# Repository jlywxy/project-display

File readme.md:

# Project Display

This is the repo sharing some of the mobile display information and their debugging method.<br>
The testing and debugging procedure are all from scratch, including PCB and firmware.<br>
See each dir for more info.<br>
*Note: <b>Display Module Specification or Display Interface Specification are NOT supplied.</b><br>

License: GPLv2<br>

Display Interface|Display Type|Brand|Bridge|Size|Part No.|Link
-|-|-|-|-|-|-
JEIDA LVDS|LCD|AUO|FPGA|7.0|G070VW01 V0|<a href='//github.com/jlywxy/project-display/lvds-lcd-auo-fpga'>lvds-lcd-auo-fpga</a>
MIPI DSI|LCD|Sharp|SSD2828|5.0|LS050T1SX01|<a href='//github.com/jlywxy/project-display/mipi-lcd-sharp-ssd2828'>mipi-lcd-sharp-ssd2828</a>
RGB UPS051|LCD|AUO|FPGA|3.0|A030DW01 / A030DW02|<a href='//github.com/jlywxy/project-display/parallel-lcd-auo-fpga'>parallel-lcd-auo-fpga</a>
RGB|LCD|LG Display|CPLD/FPGA|5.0|LD050WV1-SD01|<a href='//github.com/jlywxy/project-display/rgb-lcd-lg-cpld'>rgb-lcd-lg-cpld</a>
RGB|LCD|LG Display|STM32|5.0|LD050WV1-SD01|<a href='//github.com/jlywxy/project-display/rgb-lcd-lg-stm32'>rgb-lcd-lg-stm32</a>

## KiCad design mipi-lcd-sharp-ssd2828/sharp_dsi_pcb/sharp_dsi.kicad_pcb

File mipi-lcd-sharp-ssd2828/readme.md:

# Driving MIPI-DSI LCD(Sharp LS050T1SX01) using SSD2828

This project is testing the PCB layout of MIPI D-PHY high-speed differential and driving Sharp LS050T1SX01 using SSD2828 D-PHY and DSI bridge(Solomon Systech) and STM32F030F4 from scratch.

Author: jlywxy (jlywxy@outlook.com)<br>
Document Version: 1.4
- --
## Signal Wiring Brief
```
(any)  |  
       | < (parallel RGB)
       v
    SSD2828 ---------> Sharp LS050T1SX01
       ^       ^ (MIPI D-PHY & DSI)
       | < (SPI)
STM32  |  
```
- --
## Intention of the project
1. A PCB is made and tested, with MIPI D-PHY high-speed differential layouts and reverse voltage generator circuits.<br>
Checkout <a href="sharp_dsi_pcb">sharp_dsi_pcb</a> directory for PCB designed using KiCad.
2. Test method is using SSD2828 BIST mode and LCD bist mode (provided by LCD driver R63311) to display color at full screen and using the builtin test mode in the LCD. <br>
The testing signal frequency output from SSD2828 is now 992 MHz (0.99GHz), with ideal frame rate at 120 Hz.<br>

- --

## Circuit Schematic Suggestions

1. Use reverse voltage generator IC for LCD AVDD+/-.<br>
Currently using ICL7660 from Renesas.
2. Put KiCad PWR_FLAG at VBUS/GND at USB-C connector.
3. Use 3.3v LDO to VDDIO for LCD, SSD2828 and STM32.
- --

## High-Speed Signal Integrity for D-PHY

1. The board in this project is 2-layered, with the coplanar impedance control.<br>
2. Make sure D-PHY differential wiring has 100-Ohm differential impedance and 50-Ohm single end impedance. ()<br>
The width and space of the wiring should be calculated by the PCB impedance calculator or EDA-integrated tools. <br>
In this board, the Coplanar Differential Impedance is used. Since the restriction of 2-layer board, <b>the final impedance was controlled as 100-Ohm differential and 68-Ohm single-ended.</b><br>

* Note: for the difference of MIPI DSI and MIPI D-PHY, refer to `Misc->Knowledge Bases of Concepts` in this article.

## PCB Layout and Manufacturing Suggestions
1. For D-PHY Differential Layout
* Use a professional tool to design such a high-speed board, such as KiCad(using in this project)/Altium/Cadence.
* The D-PHY lines have to use vias going into the internal space of the connector.
```
------------------......
| | | | | | |
 ø ø ø ø ø ø ......
ø ø ø ø ø ø 
 | | | | | | | ......
------------------

("|"=pad, "ø"=via-holes)
```
2. For connector soldering and layout
* Do not use heat gun to solder plastic components, even if temperature is lower than 260(C).
* Do not use low temperature soldering tin (accurately 138(C)Bi-Sn), which is not rock-hard then spliting apart and cause <b>rosin joint</b>
* Make connector direction easy for LCD connection.
* Make soldering pad bigger and longer to conveniently solder connector on the board.
* To solder connector on the board using iron, put tin and rosin on the footprint of PCB, then remove them to make a thin layer. Put tin on the iron header, and put connector on the PCB, use iron header to touch connector pin, especially reload the tin in the pad on the PCB. If tin on the pad are gathering together, dip some rosin to the PCB to make them apart, or use copper strip to suck the tin off. After soldering, a visual check should be applied as: tin should connect the pad surface and connector pin, making a small tin curve; no tin is still gathering.
3. For PCB Manufacturing
* Use KiCad to plot Gerber and drill files, then zip the files and send to manufacture.
* It is tested using JLCPCB to manufacture the board.
The gerber settings for JLCPCB manufacture should be modified as follow:

||-Gerber Options-|
|-|-|
|*[yes]|Use Protel filename extensions|
|*[no]|Generate Gerber job file|
|*[yes]|Subtract soldermask from silkscreen|
4.6, unit mm|Coordinate format|
|*[no]|USe extended X2 format(recommended)|
|*[no]|Include netlist attributes|
|[no]|Disable aperture macros(not recommended)|

||-Drill Units-|
|-|-|
|*[yes]|Millimeters|
|[no]|Inches|

Note: *=modified options compared to the default settings

4. If some IC provided suggested circuit PCB layout, follow their instructions.
- --
## Code Packaging For MIPI Packet Transfer
* Functions implemented: 
```
1. setting/reading SSD2828 registers, 
2. writing MIPI short/long DCS/General registers/commands,
3. reading short DCS/General registers.
```
```c
void SSD_SPI_Write(uint8_t *buf,int length){
    HAL_SPI_Transmit(&hspi1,buf,length,HAL_TIMEOUT);
}
void SSD_SPI_Read(int length, uint8_t *r){
    HAL_SPI_Receive(&hspi1,r,length,HAL_TIMEOUT);
}
void SSD_SPI_ReadWrite(uint8_t *buf, int length, uint16_t *r){
    volatile uint16_t bufr[10];
    HAL_SPI_TransmitReceive(&hspi1, buf, (uint8_t *) bufr, length + 2, HAL_TIMEOUT);
    volatile uint8_t byter0=0|bufr[length]>>1;
    volatile uint8_t byter1=0|((bufr[length]&0b000000001)<<7)|(bufr[length+1]>>2);
    r[0]=byter0;
    r[1]=byter1;
}
uint16_t SSD_SPI_ReadReg(uint8_t reg){
    uint16_t tbuf[2];
    tbuf[0]=reg;
    tbuf[1]=0xfa;
    uint16_t rbuf[2];
    SSD_SPI_ReadWrite((uint8_t*)tbuf,2,rbuf);
    return rbuf[0]|rbuf[1]<<8;

}

void SSD_SPI_WriteReg(uint8_t reg,uint16_t data,int len){
    uint16_t buf[3]={reg,1<<8|(data&0xff),1<<8|((data>>8)&0xff)};
    SSD_SPI_Write(buf,len+1);
}

void SSD_MIPI_WriteLongGeneric(uint8_t reg,uint16_t* data,int len){
    SSD_SPI_WriteReg(0xb7,0x0302,2);
    SSD_SPI_WriteReg(0xb8,0x0000,2);
    SSD_SPI_WriteReg(0xbc,len,2);
    uint16_t b0[1]={0xbf};
    SSD_SPI_Write(b0,1);
    uint16_t b1[1]={1<<8|reg};
    SSD_SPI_Write(b1,1);
    for(int i=0;i<len-1;i++){
        uint16_t b2[1]={1<<8|data[i]};
        SSD_SPI_Write(b2,1);
    }
}
void SSD_MIPI_WriteLongDCS(uint8_t reg,uint16_t* data,int len){
    SSD_SPI_WriteReg(0xb7,0x0050,2);
    SSD_SPI_WriteReg(0xb8,0x0000,2);
    SSD_SPI_WriteReg(0xbc,len,2);
    uint16_t b0[1]={0xbf};
    SSD_SPI_Write(b0,1);
    uint16_t b1[1]={1<<8|reg};
    SSD_SPI_Write(b1,1);
    for(int i=0;i<len-1;i++){
        uint16_t b2[1]={1<<8|data[i]};
        SSD_SPI_Write(b2,1);
    }

}
void SSD_MIPI_WriteShortGeneric(uint8_t reg,uint16_t data,int len){
    uint16_t b[2]={data&0xff,data>>8};
    SSD_MIPI_WriteLongGeneric(reg,b,len);
}
void SSD_MIPI_WriteShortDCS(uint8_t reg,uint16_t data,int len){
    uint16_t b[2]={data&0xff,data>>8};
    SSD_MIPI_WriteLongDCS(reg,b,len);
}
uint16_t SSD_MIPI_ReadGeneric(uint8_t reg,uint16_t *len, uint16_t *status){
    SSD_SPI_WriteReg(0xb7,0x0382,2);
    SSD_SPI_WriteReg(0xc1,0x0002,2);
    SSD_SPI_WriteReg(0xc0,0x0001,2);

    SSD_SPI_WriteReg(0xbc,0x0001,2);
    SSD_SPI_WriteReg(0xbf,reg,2);
        *len=SSD_SPI_ReadReg(0xc2);
        if((SSD_SPI_ReadReg(0xc6)&1)==0){
            *status=1;
        }else{
            *status=0;
        }
        if(SSD_SPI_ReadReg(0xc3)!=0){
            *status=2;
        }else{
            *status=0;
        }
    return SSD_SPI_ReadReg(0xff);
}
uint16_t SSD_MIPI_ReadDCS(uint8_t reg,uint16_t *len, uint16_t *status){
    SSD_SPI_WriteReg(0xb7,0x03c2,2);
    SSD_SPI_WriteReg(0xc1,0x00ff,2);
    SSD_SPI_WriteReg(0xc0,0x0002,2);

    SSD_SPI_WriteReg(0xbc,0x0001,2);
    SSD_SPI_WriteReg(0xbf,reg,2);
        *len=SSD_SPI_ReadReg(0xc2);
        if((SSD_SPI_ReadReg(0xc6)&1)==0){
            *status=1;
        }else{
            *status=0;
        }
        if(SSD_SPI_ReadReg(0xc3)!=0){
            *status=2;
        }else{
            *status=0;
        }
    return SSD_SPI_ReadReg(0xff);
}
```

- --
## Overview of the LCD Module

### 1. Display Interface

This LCD is using MIPI D-PHY differential signal interface.

| Signal Electrical-Level | Speed | Driver IC |
|-|-|-|
|1.2v-330mV-MIPI-D-PHY   | 500 MHz | Renesas R63311

|Signal Wires| Power Supply|
|-|-|
|1-port-MIPI-D-PHY(4lanes(2 clk, 8 data) | VDD(1.8, 3.3v), Bias(±5v)|

### 2. Backlight Interface

This LCD requires 19.8v dual power with each 20mA current limit without internal backlight driver.

### 3. Connector

The part number of Mating connector is AYF333135 of Panasonic, which has 31pins with crossing 0.3mm interval.

This is the only connector of the LCD to provide data/control/backlight connection.

- --

## Display Workflow(Steps to light up display in Brief)

0. Backlight power on. (Async)
1. LCD/STM32/SSD2828 VDD/MVDD on; ICL7660 V+ on; LCD/SSD2828 XRES.
2. Init SSD2828: set LP mode, PLL, VSYNC/HSYNC, color mode, BIST... 
3. Init LCD via SSD2828: unlock command write, ..., DISPON, SLEEPOFF
4. SSD2828 enters HS Video Mode, starting video transmission.

- --
## Misc

### LCD Module Optical Characteristics

|Pixel-Arrangement   | Panel-Type | Color-Depth|
|---------------------|-------------|---------------|
|RGB vertical stripe | IPS        | 8bit (16.7M)|

|Contrast | Color-Chromaticity | Backlight|
|----------|--------------------|-------------------|
|1000:1   | 72% NTSC           | 450 nits|

### Knowledge Bases of Concepts

1. MIPI DSI
* The MIPI Alliance defines modern interface of mobile devices like phones, including display, cameras, etc. 
* The DSI defined a protocol for LCD to transfer data at a fast speed using a serial bus.<br>
Its applicational protocol is still DPI/RGB.<br>
Since the protocol is complex, please refer to MIPI Alliance Standard for Display Serial Interface.
2. MIPI D-PHY
* The D-PHY defined the physical(electrical) specification for the high-speed transfer.<br>
For more detailed information, please refer to MIPI Alliance Specification for D-PHY.
3. MIPI DCS: DCS command and Generic command
The DCS command set is defined by MIPI alliance, which are common and standard through different types of LCDs, such as 0x29/0x11. <br>
For the detailed command list, refer to MIPI Alliance Specification for Display Command Set.
The Generic command set was defined by the LCD manufacture out of the standard.<br>

4. MIPI-DPI/RGB/LTDC

* MIPI Display Pixel Interface (MIPI-DPI) is one of the MIPI display interface series, which is well known as RGB/Parallel/LTDC interface. This interface splits control lines(HSYNC/VSYNC/DE) with data lines(RGB parallel lines). Since it uses single-ended signals(compared to MIPI D-PHY), the max speed(clock speed) could be limited, but it can transfer full pixel data in one clock period(compared to serial interfaces). The color depth is configurable as RGB565/RGB666/RGB888 and more, which could also be 'hacked' to leave out some pins or branch some lines(when downsampling color depth, throw away certain LSB; when upsampling, branch certain MSB to LSB or connect certain LSB to GND).
```
RGB888 (typical format of 16.7M color display)
-------------------------------------------------
       RRRRRRRR GGGGGGGG BBBBBBBB (3 bytes)

RGB666 (typical format of 262k color display, and 16.2M color TN panels with FRC)
-------------------------------------------------
             RR RRRRGGGG GGBBBBBB (18 bits)

RGB565
-------------------------------------------------
                RRRRRGGG GGGBBBBB (2 bytes)

RGB101010 (not available in most of the displays, typical format of 1.07B color screen)
-------------------------------------------------
RRRRRR RRRRGGGG GGGGGGBB BBBBBBBB (30 bits)
```

4. Low-Temperature Soldering Tin

* A type of soldering tin which melting point is only 138 celsius high. It has 58% Bismuth(Bi) and 42% Stannum(Sn) to make such a low melting point. This temperature is so important for those not heat-resistant components such as LEDs and MEMS components. However, it's definitely not recommended for connector soldering, which will cause unsoldering and rosin-joint, because this type of soldering tin is fragile.

### Another performance tests
1. SSD2828 and LCD overclock is viable.(See Availablity part above)
2. Using 3.3v or lower voltage for LCD AVDD+/- may still take the screen 'alive', but with lower brightness.

### Project status
This project works has been done.</b> The document and code comments are still needed to be finshed and polished.
<br>
```
Current Progress

[ok] finding LCD Specification sheet
[ok] finding LCD Driver IC sheet
[ok] SSD2828 SPI Transmission and Initialization setup
[ok] SSD2828 and LCD MIPI configuration setup
[ok] Circuit Schematic design
[ok] PCB Layout and MIPI Differential Layout design
[ok] Test and Debug
(done)
```

### Further Recommendations and Information

1. Use one chip for LCD Backlight(Boost ciruits) and AVDD(Bias), as: TI LM36274, which includes Backlight Boost with Dimming, I2C control, and Bias voltage output.
2. Use the same package of LDOs.
3. Put connector to a more convenient position for LCD connection.
4. Specification datasheets of LCDs, their controllers and standards are not included in this repository, since the author do not have their copyrights and not a member of any alliances(MIPI alliance, VESA, USB-IF, etc). Instead, however, they may be available to the public in some websites, which is the place to get the docs for non-commercial and development purposes.

5. Stay informed of a new project of a USB-C single input (usb-c alternative mode/billboard device, integrated power boost circuits) external display hardware(the "udisplay").

### Document Patch and Errata

* Corrected the fause phrase in the paragraph "Display Workflow": corrected to "Enters HS Mode", rather than formerly "Enters HP Mode". 
* Corrected LCD performance description of the paragraph "Misc".  72% NTSC is not fully equal to 100% sRGB.<br>

patch above: jlywxy@2022.12.18

* Fixed document format problem: charts.<br>

patch above: jlywxy@2023.2.8<br>

* Modified the PCB design tool restriction: LCEDA now being able to tune wire length of differential pair.<br>
* Added Paragraph "High-Speed Signal Integrity" for more detailed D-PHY layout guide.<br>
* Corrected the calling for D-PHY.
* Implemented `Knowledge Bases of Concepts` part.

patch above: jlywxy@2023.3.19<br>

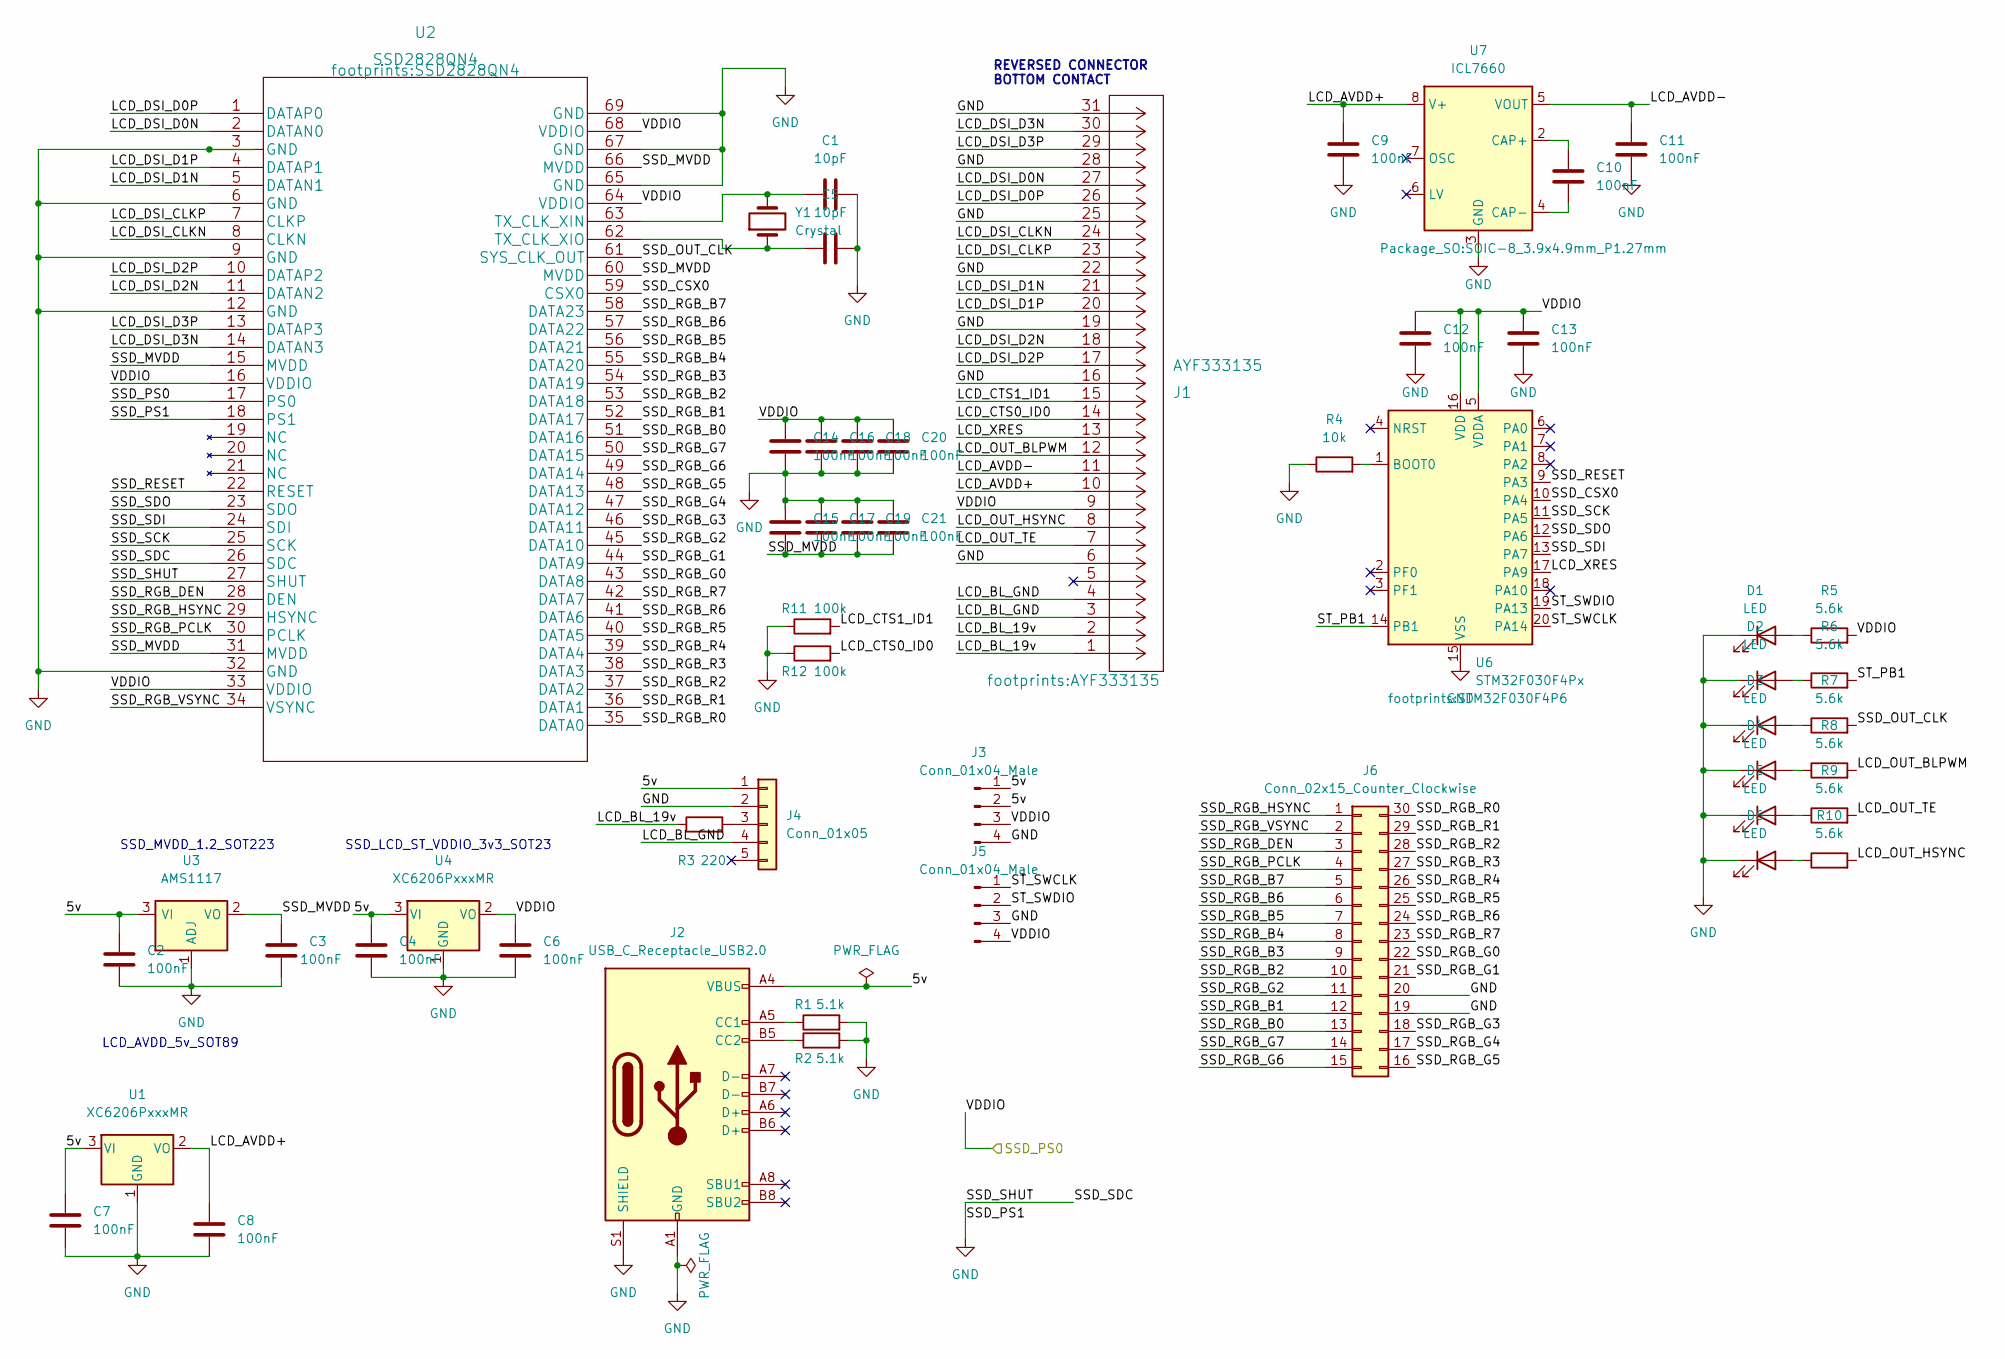
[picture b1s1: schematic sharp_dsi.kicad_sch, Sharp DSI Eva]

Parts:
C1, C5: 10pF; C_0402_1005Metric
C2, C3, C4, C6, C7, C8, C9, C10, C11, C12, C13, C14, C15, C16, C17, C18, C19, C20, C21: 100nF; C_0402_1005Metric
D1, D2, D3, D4, D5, D6: LED; R_0603_1608Metric
J1: AYF333135
J2: USB_C_Receptacle_USB2.0; USB_C_Receptacle_HRO_TYPE-C-31-M-12
J3, J5: Conn_01x04_Male; PinHeader_1x04_P2.54mm_Vertical
J4: Conn_01x05; PinHeader_1x05_P2.54mm_Vertical
J6: Conn_02x15_Counter_Clockwise; PinHeader_2x15_P2.54mm_Vertical
R1, R2: 5.1k; R_0603_1608Metric
R3: 220; R_Box_L8.4mm_W2.5mm_P5.08mm
R4: 10k; R_0603_1608Metric
R5, R6, R7, R8, R9, R10: 5.6k; R_0603_1608Metric
R11, R12: 100k; R_0603_1608Metric
U1: XC6206PxxxMR; XC6206P502PR
U2: SSD2828QN4
U3: AMS1117; SOT-223-3_TabPin2
U4: XC6206PxxxMR; SOT-23
U6: STM32F030F4Px; STM32F030F4P6
U7: ICL7660; SOIC-8_3.9x4.9mm_P1.27mm
Y1: Crystal; Crystal_SMD_5032-2Pin_5.0x3.2mm

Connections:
/5v: C2.1, C4.1, C7.1, J2.A4 (VBUS), J2.A9 (VBUS), J2.B4 (VBUS), J2.B9 (VBUS), J3.1, J3.2, J4.1, U1.3 (VI), U3.3 (VI), U4.3 (VI)
/LCD_AVDD+: C8.1, C9.1, J1.10, U1.2 (VO), U7.8 (V+)
/LCD_AVDD-: C11.1, J1.11, U7.5 (VOUT)
/LCD_BL_19v: J1.1, J1.2, R3.1
/LCD_BL_GND: J1.3, J1.4, J4.4
/LCD_CTS0_ID0: J1.14, R12.2
/LCD_CTS1_ID1: J1.15, R11.2
/LCD_DSI_CLKN: J1.24, U2.8 (CLKN)
/LCD_DSI_CLKP: J1.23, U2.7 (CLKP)
/LCD_DSI_D0N: J1.27, U2.2 (DATAN0)
/LCD_DSI_D0P: J1.26, U2.1 (DATAP0)
/LCD_DSI_D1N: J1.21, U2.5 (DATAN1)
/LCD_DSI_D1P: J1.20, U2.4 (DATAP1)
/LCD_DSI_D2N: J1.18, U2.11 (DATAN2)
/LCD_DSI_D2P: J1.17, U2.10 (DATAP2)
/LCD_DSI_D3N: J1.30, U2.14 (DATAN3)
/LCD_DSI_D3P: J1.29, U2.13 (DATAP3)
/LCD_OUT_BLPWM: J1.12, R8.2
/LCD_OUT_HSYNC: J1.8, R10.2
/LCD_OUT_TE: J1.7, R9.2
/LCD_XRES: J1.13, U6.17 (PA9)
/SSD_CSX0: U2.59 (CSX0), U6.10 (PA4)
/SSD_MVDD: C3.1, C15.2, C17.2, C19.2, C21.2, U2.15 (MVDD), U2.31 (MVDD), U2.60 (MVDD), U2.66 (MVDD), U3.2 (VO)
/SSD_OUT_CLK: R7.2, U2.61 (SYS_CLK_OUT)
/SSD_PS0: C6.1, C12.2, C13.2, C14.1, C16.1, C18.1, C20.1, J1.9, J3.3, J5.4, R5.2, U2.16 (VDDIO), U2.17 (PS0), U2.33 (VDDIO), U2.64 (VDDIO), U2.68 (VDDIO), U4.2 (VO), U6.5 (VDDA), U6.16 (VDD)
/SSD_RESET: U2.22 (RESET), U6.9 (PA3)
/SSD_RGB_B0: J6.13, U2.51 (DATA16)
/SSD_RGB_B1: J6.12, U2.52 (DATA17)
/SSD_RGB_B2: J6.10, U2.53 (DATA18)
/SSD_RGB_B3: J6.9, U2.54 (DATA19)
/SSD_RGB_B4: J6.8, U2.55 (DATA20)
/SSD_RGB_B5: J6.7, U2.56 (DATA21)
/SSD_RGB_B6: J6.6, U2.57 (DATA22)
/SSD_RGB_B7: J6.5, U2.58 (DATA23)
/SSD_RGB_DEN: J6.3, U2.28 (DEN)
/SSD_RGB_G0: J6.22, U2.43 (DATA8)
/SSD_RGB_G1: J6.21, U2.44 (DATA9)
/SSD_RGB_G2: J6.11, U2.45 (DATA10)
/SSD_RGB_G3: J6.18, U2.46 (DATA11)
/SSD_RGB_G4: J6.17, U2.47 (DATA12)
/SSD_RGB_G5: J6.16, U2.48 (DATA13)
/SSD_RGB_G6: J6.15, U2.49 (DATA14)
/SSD_RGB_G7: J6.14, U2.50 (DATA15)
/SSD_RGB_HSYNC: J6.1, U2.29 (HSYNC)
/SSD_RGB_PCLK: J6.4, U2.30 (PCLK)
/SSD_RGB_R0: J6.30, U2.35 (DATA0)
/SSD_RGB_R1: J6.29, U2.36 (DATA1)
/SSD_RGB_R2: J6.28, U2.37 (DATA2)
/SSD_RGB_R3: J6.27, U2.38 (DATA3)
/SSD_RGB_R4: J6.26, U2.39 (DATA4)
/SSD_RGB_R5: J6.25, U2.40 (DATA5)
/SSD_RGB_R6: J6.24, U2.41 (DATA6)
/SSD_RGB_R7: J6.23, U2.42 (DATA7)
/SSD_RGB_VSYNC: J6.2, U2.34 (VSYNC)
/SSD_SCK: U2.25 (SCK), U6.11 (PA5)
/SSD_SDI: U2.24 (SDI), U6.13 (PA7)
/SSD_SDO: U2.23 (SDO), U6.12 (PA6)
/ST_PB1: R6.2, U6.14 (PB1)
/ST_SWCLK: J5.1, U6.20 (PA14)
/ST_SWDIO: J5.2, U6.19 (PA13)
GND: C1.2, C2.2, C3.2, C4.2, C5.2, C6.2, C7.2, C8.2, C9.2, C11.2, C12.1, C13.1, C14.2, C15.1, C16.2, C17.1, C18.2, C19.1, C20.2, C21.1, D1.1 (K), D2.1 (K), D3.1 (K), D4.1 (K), D5.1 (K), D6.1 (K), J1.6, J1.16, J1.19, J1.22, J1.25, J1.28, J1.31, J2.A1 (GND), J2.A12 (GND), J2.B1 (GND), J2.B12 (GND), J2.S1 (SHIELD), J3.4, J4.2, J5.3, J6.19, J6.20, R1.2, R2.2, R4.1, R11.1, R12.1, U1.1 (GND), U2.3 (GND), U2.6 (GND), U2.9 (GND), U2.12 (GND), U2.18 (PS1), U2.26 (SDC), U2.27 (SHUT), U2.32 (GND), U2.65 (GND), U2.67 (GND), U2.69 (GND), U3.1 (ADJ), U4.1 (GND), U6.15 (VSS), U7.3 (GND)
unnamed: C1.1, U2.63 (TX_CLK_XIN), Y1.2
unnamed: C5.1, U2.62 (TX_CLK_XIO), Y1.1
unnamed: C10.1, U7.2 (CAP+)
unnamed: C10.2, U7.4 (CAP-)
unnamed: D1.2 (A), R5.1
unnamed: D2.2 (A), R6.1
unnamed: D3.2 (A), R7.1
unnamed: D4.2 (A), R8.1
unnamed: D5.2 (A), R9.1
unnamed: D6.2 (A), R10.1
unnamed: J2.A5 (CC1), R1.1
unnamed: J2.B5 (CC2), R2.1
unnamed: J4.3, R3.2
unnamed: R4.2, U6.1 (BOOT0)

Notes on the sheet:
REVERSED CONNECTOR BOTTOM CONTACT
SSD_MVDD_1.2_SOT223
SSD_LCD_ST_VDDIO_3v3_SOT23
LCD_AVDD_5v_SOT89

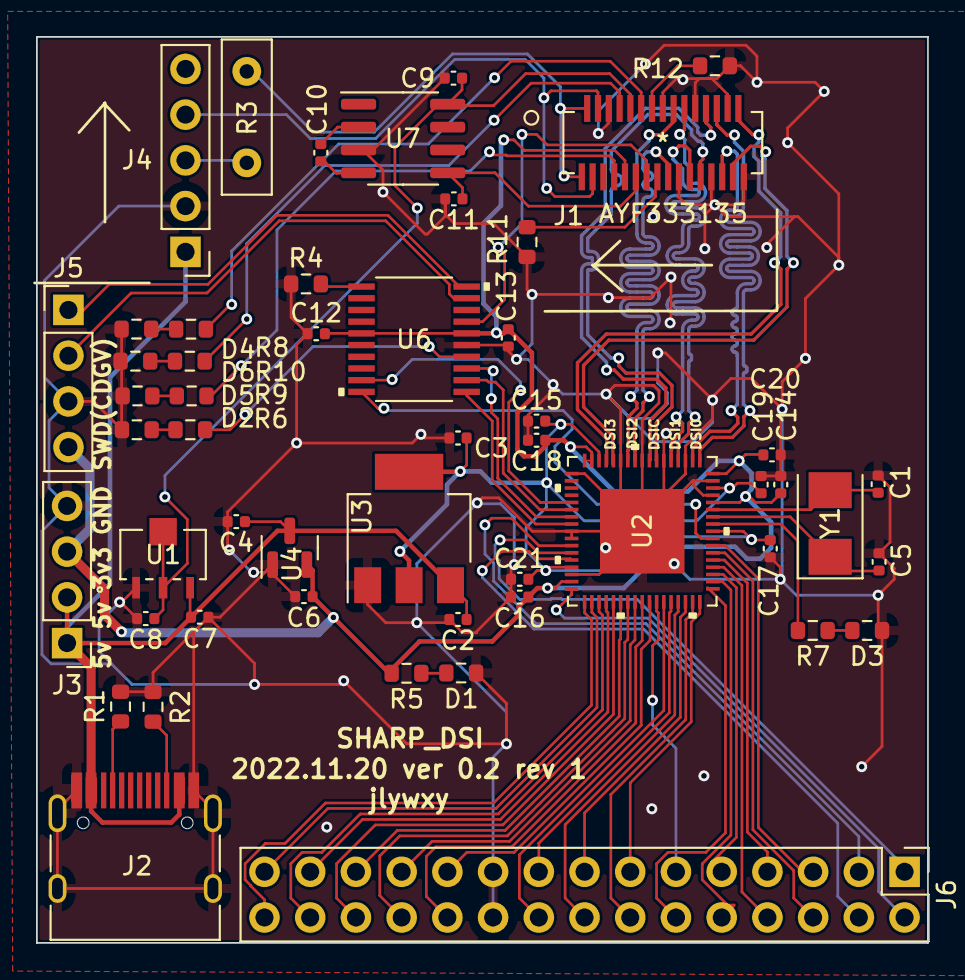
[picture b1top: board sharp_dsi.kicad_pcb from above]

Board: 2 copper layers, 49.5 x 50.3 mm, 52 parts (0 on the bottom side), 75 nets.

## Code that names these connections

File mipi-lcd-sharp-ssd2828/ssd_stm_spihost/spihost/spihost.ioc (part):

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Mcu.Name=STM32F030F4Px
Mcu.Package=TSSOP20
Mcu.UserName=STM32F030F4Px
PA13.Mode=Serial_Wire
PA13.Signal=SYS_SWDIO
PA14.Mode=Serial_Wire
PA14.Signal=SYS_SWCLK
PA3.Signal=GPIO_Output
PA4.Mode=NSS_Signal_Hard_Output
PA4.Signal=SPI1_NSS
PA5.Mode=Full_Duplex_Master
PA5.Signal=SPI1_SCK
PA6.Mode=Full_Duplex_Master
PA6.Signal=SPI1_MISO
PA7.Mode=Full_Duplex_Master
PA7.Signal=SPI1_MOSI
PA9.Signal=GPIO_Output
PB1.Signal=GPIO_Output
RCC.SYSCLKFreq_VALUE=8000000
board=custom

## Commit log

2023-04-09 project-display initial commit

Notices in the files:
parts and their libraries:
Copyright 2021 Accelerated Designs. All rights reserved.
